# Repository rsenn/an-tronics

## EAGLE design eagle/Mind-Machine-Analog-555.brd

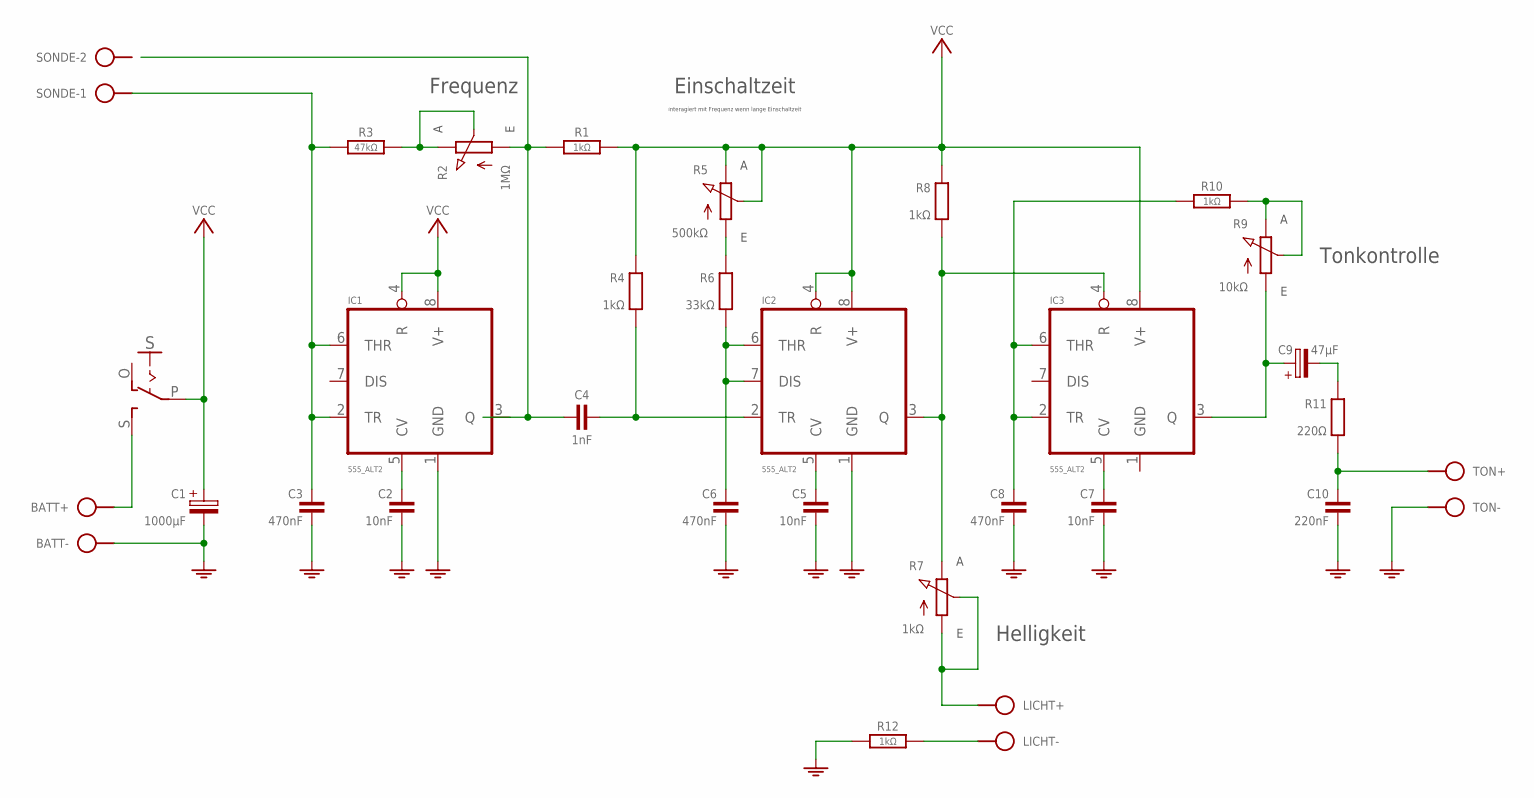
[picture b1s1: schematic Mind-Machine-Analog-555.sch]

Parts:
BATT: SPAD+-+-; SPAD+-
C1: 1000µF; E5-6
C2, C5, C7: 10nF; C025-025X050
C3, C6, C8: 470nF; C025-025X050
C4: 1nF; C050-020X044
C9: 47µF; E2,5-4
C10: 220nF; C025-025X050
IC1, IC2, IC3: 555_ALT2; DIL08
LICHT: SPAD+--+; SPAD-+
R1, R10, R12: 1kΩ; 0204/10
R2: 1MΩ; POT
R3: 47kΩ; 0204/10
R4, R8: 1kΩ; 0204/10-V
R5: 500kΩ; POT
R6: 33kΩ; 0204/10-V
R7: 1kΩ; POT
R9: 10kΩ; POT
R11: 220Ω; 0204/10-V
S: SL-SW-1P-2T; SLSW-1P2T
SONDE: SPAD-2
TON: SPAD+-+-; SPAD+-

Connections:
GND: BATT.1, C1.-, C2.2, C3.2, C5.2, C6.2, C7.2, C8.2, C10.2, IC1.1 (GND), IC2.1 (GND), IC3.1 (GND), R12.1, TON.1
unnamed: C5.1, IC2.5 (CV)
unnamed: BATT.2, S.S
unnamed: R2.E, R2.S, R3.2
unnamed: C4.1, IC1.3 (Q), R1.1, R2.A
unnamed: C4.2, IC2.2 (TR), R4.2 (1)
unnamed: C3.1, IC1.2 (TR), IC1.6 (THR), R3.1, SONDE.1
unnamed: C2.1, IC1.5 (CV)
unnamed: R5.A, R6.1 (2)
unnamed: C6.1, IC2.6 (THR), IC2.7 (DIS), R6.2 (1)
unnamed: IC2.3 (Q), IC3.4 (R), R7.E, R8.2 (1)
unnamed: LICHT.2, R7.A, R7.S
unnamed: C8.1, IC3.2 (TR), IC3.6 (THR), R10.1
unnamed: R9.E, R9.S, R10.2
unnamed: C9.+, IC3.3 (Q), R9.A
unnamed: C9.-, R11.1 (2)
unnamed: C10.1, R11.2 (1), TON.2
unnamed: C7.1, IC3.5 (CV)
unnamed: LICHT.1, R12.2
VCC: C1.+, IC1.4 (R), IC1.8 (V+), IC2.4 (R), IC2.8 (V+), IC3.8 (V+), R1.2, R4.1 (2), R5.E, R5.S, R8.1 (2), S.P

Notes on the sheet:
Helligkeit
Frequenz
Einschaltzeit
interagiert mit Frequenz wenn lange Einschaltzeit
Tonkontrolle

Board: 2 copper layers, 30 parts (0 on the bottom side), 20 nets, no tracks yet.

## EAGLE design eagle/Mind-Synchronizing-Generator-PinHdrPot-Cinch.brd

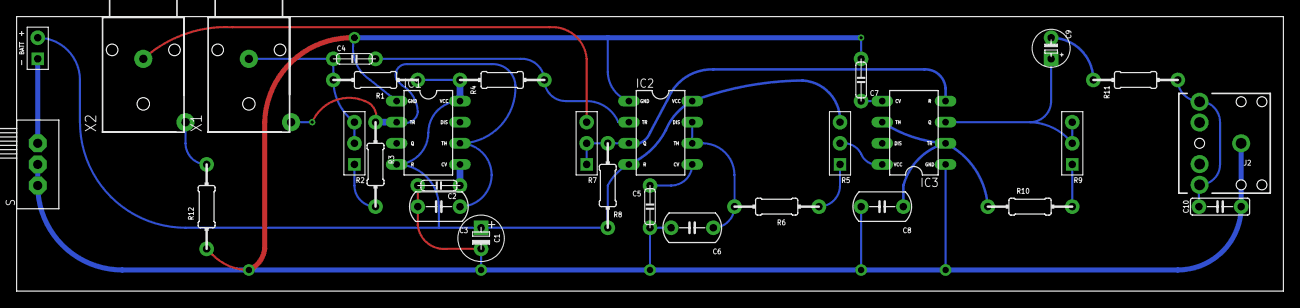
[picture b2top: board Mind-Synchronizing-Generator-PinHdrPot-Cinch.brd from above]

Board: 2 copper layers, 152.4 x 33.0 mm, 30 parts (0 on the bottom side), 20 nets.

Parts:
BATT: SPAD+--+; SPAD-+
C1: 1000µF; E2,5-6
C2: 10nF; C050-020X044
C3, C6, C8: 470nF; C050-040X075
C4: 1nF; C050-020X044
C5, C7: 10nF; C050-020X044/V
C9: 47µF; E2,5-4
C10: 220nF; C050-025X060
IC1, IC2, IC3: 555; 555-DIL
J2: AUDIO_JACK; AUDIO-JACK
R1, R10, R12: 1kΩ; 0204/10
R2: 1MΩ; CONN-3P
R3: 47kΩ; 0204/10
R4, R8: 1kΩ; 0204/10-V
R5: 500kΩ; CONN-3P
R6: 33kΩ; 0204/10
R7: 1kΩ; CONN-3P
R9: 10kΩ; CONN-3P
R11: 220Ω; 0204/10-V
S: SL-SW-1P-2T-V2; SLSW-1P2T-V2
X1, X2: CINCH-MONO-WBTOR1; WBTOR1

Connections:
GND: C1.-, C2.2, C3.2, C5.2, C6.2, C7.2, C8.2, C10.2, IC1.1, IC2.1, IC3.1, J2.SLEEVE, R12.1, S.P
unnamed: C5.1, IC2.5
unnamed: BATT.1, S.O
unnamed: R7.3, X2.U
unnamed: C4.2, IC2.2, R4.2
unnamed: C3.1, IC1.2, IC1.6, R3.1, X1.T
unnamed: C2.1, IC1.5
unnamed: R5.1, R6.1
unnamed: C6.1, IC2.6, IC2.7, R6.2
unnamed: R9.1, R10.2
unnamed: R2.1, R3.2
unnamed: C8.1, IC3.2, IC3.6, R10.1
unnamed: C9.-, R11.1
unnamed: C10.1, J2.RING, J2.TIP, R11.2
unnamed: C7.1, IC3.5
unnamed: R12.2, X2.T
Q1: C4.1, IC1.3, R1.2, R2.2, R2.3, X1.U
Q2: IC2.3, IC3.4, R7.1, R7.2, R8.2
Q3: C9.+, IC3.3, R9.2, R9.3
VCC: BATT.2, C1.+, IC1.4, IC1.8, IC2.4, IC2.8, IC3.8, R1.1, R4.1, R5.2, R5.3, R8.1

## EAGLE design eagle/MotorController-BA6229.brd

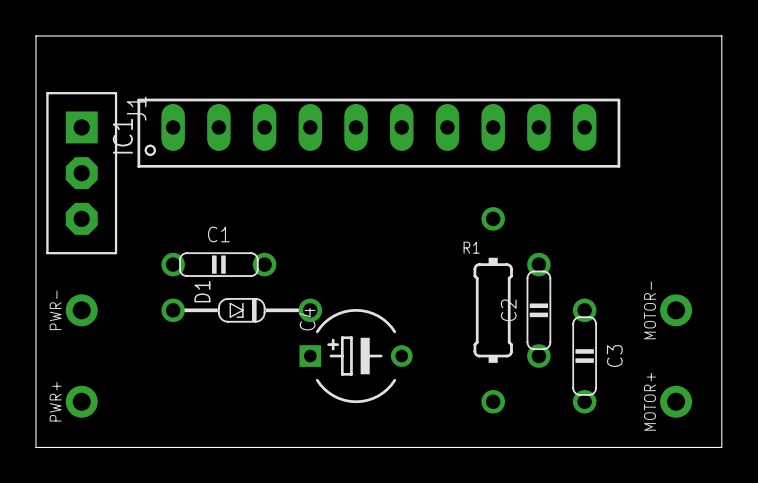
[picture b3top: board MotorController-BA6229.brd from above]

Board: 2 copper layers, 38.1 x 22.9 mm, 12 parts (0 on the bottom side), 10 nets, no tracks yet.

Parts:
C1, C2: 0.1μF; C050-020X044
C3: 0.33μF; C050-020X044
C4: 100μF; E5-5/V
D1: Z=4.7V; DO34Z7V
IC1: BA6229; SIL10
J1: CONN-3P-3P; CONN-3P
MOTOR+: SPAD
MOTOR-: SPAD
PWR+: SPAD
PWR-: SPAD
R1: 10Ω; 0204/10-V

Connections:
GND: C1.2, C2.2, C4.-, D1.A, IC1.1, J1.1, PWR-.1
unnamed: C3.1, IC1.2, MOTOR+.1
unnamed: C2.1, IC1.9
unnamed: C1.1, IC1.3
unnamed: D1.C, IC1.4
unnamed: IC1.5, J1.2
unnamed: C3.2, IC1.10, MOTOR-.1
unnamed: IC1.6, J1.3
unnamed: IC1.8, R1.1
VCC: C4.+, IC1.7, PWR+.1, R1.2

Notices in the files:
parts and their libraries:
pad: Licensing: Creative Commons ShareAlike 4.0 International - https://creativecommons.org/licenses/by-sa/4.0
